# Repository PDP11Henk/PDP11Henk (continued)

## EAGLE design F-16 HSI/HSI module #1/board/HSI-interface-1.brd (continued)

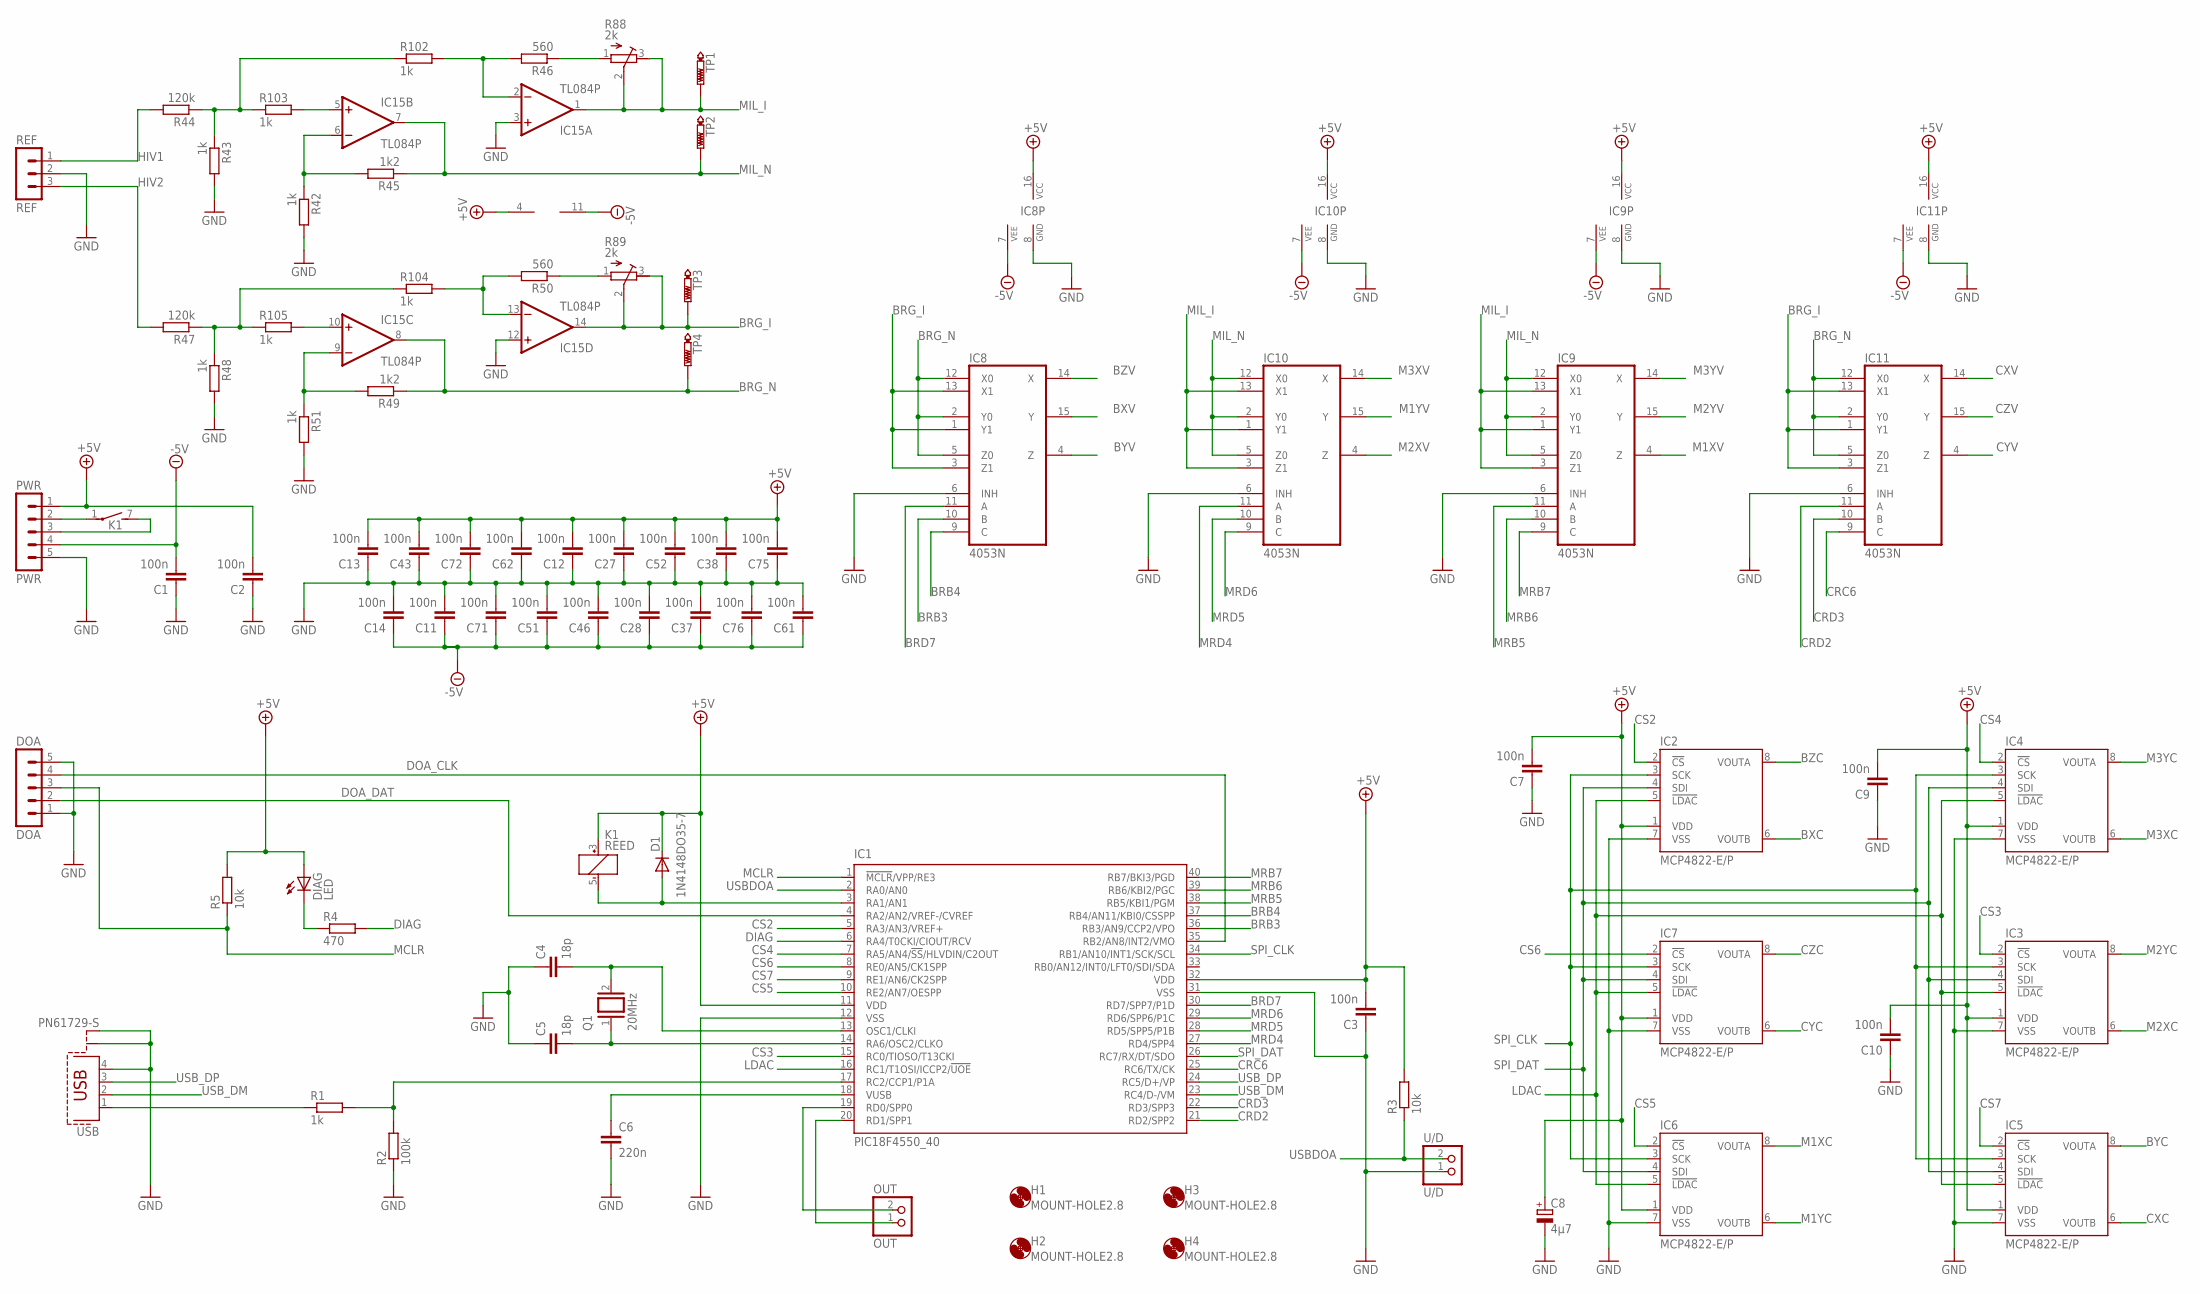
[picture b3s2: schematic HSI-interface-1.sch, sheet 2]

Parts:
C1, C2, C3, C7, C9, C10, C11, C12, C13, C14, C27, C28, C37, C38, C43, C46, C51, C52, C61, C62, C71, C72, C75, C76: 100n; C025-025X050
C4, C5: 18p; C025-025X050
C6: 220n; C5B3
C8: 4µ7; E2,5-5
D1: 1N4148DO35-7; DO35-7
DIAG: LED; LED3MM
DOA: DOA; MA05-1
H1, H2, H3, H4: MOUNT-HOLE2.8; 2,8
IC1: PIC18F4550_40; DIL40
IC2, IC3, IC4, IC5, IC6, IC7: MCP4822-E/P; DIL08
IC8, IC9, IC10, IC11: 4053N; DIL16
IC15: TL084P; DIL14
K1: REED
OUT: OUT; 1X02
PWR: PWR; MA05-1
Q1: 20MHz; QS
R1, R42, R43, R48, R51, R102, R103, R104, R105: 1k; 0204/7
R2: 100k; 0204/7
R3, R5: 10k; 0204/7
R4: 470; 0204/7
R44, R47: 120k; 0204/7
R45, R49: 1k2; 0204/7
R46, R50: 560; 0204/7
R88, R89: 2k; RTRIM64Z
REF: REF; MA03-1
TP1, TP2, TP3, TP4: PTR1PAD1-13; P1-13
U/D: U/D; 1X02
USB: PN61729-S

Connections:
+5V: C2.2, C3.2, C7.2, C8.+, C9.2, C10.2, C12.2, C13.2, C27.2, C38.2, C43.2, C52.2, C62.2, C72.2, C75.2, D1.C, DIAG.A, IC1.11 (VDD), IC1.32 (VDD), IC2.1 (VDD), IC3.1 (VDD), IC4.1 (VDD), IC5.1 (VDD), IC6.1 (VDD), IC7.1 (VDD), IC8.16 (VCC), IC9.16 (VCC), IC10.16 (VCC), IC11.16 (VCC), IC15.4 (V+), K1.3 (+), PWR.1, R3.2, R5.2; also elsewhere on the board
-5V: C1.2, C11.1, C14.1, C28.1, C37.1, C46.1, C51.1, C61.1, C71.1, C76.1, IC8.7 (VEE), IC9.7 (VEE), IC10.7 (VEE), IC11.7 (VEE), IC15.11 (V-), PWR.4; also elsewhere on the board
BRB3: IC1.36 (RB3/AN9/CCP2/VPO), IC8.10 (B)
BRB4: IC1.37 (RB4/AN11/KBI0/CSSPP), IC8.9 (C)
BRD7: IC1.30 (RD7/SPP7/P1D), IC8.11 (A)
BRG_I: IC8.1 (Y1), IC8.3 (Z1), IC8.13 (X1), IC11.1 (Y1), IC11.3 (Z1), IC11.13 (X1), IC15.14 (OUT), R89.2 (S), R89.3 (A), TP3.TP
BRG_N: IC8.2 (Y0), IC8.5 (Z0), IC8.12 (X0), IC11.2 (Y0), IC11.5 (Z0), IC11.12 (X0), IC15.8 (OUT), R49.1, TP4.TP
BXC: IC2.6 (VOUTB); also elsewhere on the board
BXV: IC8.15 (Y); also elsewhere on the board
BYC: IC5.8 (VOUTA); also elsewhere on the board
BYV: IC8.4 (Z); also elsewhere on the board
BZC: IC2.8 (VOUTA); also elsewhere on the board
BZV: IC8.14 (X); also elsewhere on the board
CRC6: IC1.25 (RC6/TX/CK), IC11.9 (C)
CRD2: IC1.21 (RD2/SPP2), IC11.11 (A)
CRD3: IC1.22 (RD3/SPP3), IC11.10 (B)
CS2: IC1.5 (RA3/AN3/VREF+), IC2.2 (!CS)
CS3: IC1.15 (RC0/TIOSO/T13CKI), IC3.2 (!CS)
CS4: IC1.7 (RA5/AN4/!SS!/HLVDIN/C2OUT), IC4.2 (!CS)
CS5: IC1.10 (RE2/AN7/OESPP), IC6.2 (!CS)
CS6: IC1.8 (RE0/AN5/CK1SPP), IC7.2 (!CS)
CS7: IC1.9 (RE1/AN6/CK2SPP), IC5.2 (!CS)
CXC: IC5.6 (VOUTB); also elsewhere on the board
CXV: IC11.14 (X); also elsewhere on the board
CYC: IC7.6 (VOUTB); also elsewhere on the board
CYV: IC11.4 (Z); also elsewhere on the board
CZC: IC7.8 (VOUTA); also elsewhere on the board
CZV: IC11.15 (Y); also elsewhere on the board
DIAG: IC1.6 (RA4/T0CKI/CIOUT/RCV), R4.2
DOA_CLK: DOA.4, IC1.35 (RB2/AN8/INT2/VMO)
DOA_DAT: DOA.2, IC1.4 (RA2/AN2/VREF-/CVREF)
GND: C1.1, C2.1, C3.1, C4.1, C5.1, C6.2, C7.1, C8.-, C9.1, C10.1, C11.2, C12.1, C13.1, C14.2, C27.1, C28.2, C37.2, C38.1, C43.1, C46.2, C51.2, C52.1, C61.2, C62.1, C71.2, C72.1, C75.1, C76.2, DOA.1, DOA.5, IC1.12 (VSS), IC1.31 (VSS), IC2.7 (VSS), IC3.7 (VSS), IC4.7 (VSS), IC5.7 (VSS), IC6.7 (VSS), IC7.7 (VSS), IC8.6 (INH), IC8.8 (GND), IC9.6 (INH), IC9.8 (GND), IC10.6 (INH), IC10.8 (GND), IC11.6 (INH), IC11.8 (GND), IC15.3 (+IN), IC15.12 (+IN), PWR.5, R2.1, R42.2, R43.2, R48.2, R51.2, REF.2, U/D.1, USB.4, USB.S1, USB.S2; also elsewhere on the board
HIV1: R44.2, REF.1
HIV2: R47.2, REF.3
LDAC: IC1.16 (RC1/T1OSI/ICCP2/!UOE), IC2.5 (!LDAC), IC3.5 (!LDAC), IC4.5 (!LDAC), IC5.5 (!LDAC), IC6.5 (!LDAC), IC7.5 (!LDAC)
M1XC: IC6.8 (VOUTA); also elsewhere on the board
M1XV: IC9.4 (Z); also elsewhere on the board
M1YC: IC6.6 (VOUTB); also elsewhere on the board
M1YV: IC10.15 (Y); also elsewhere on the board
M2XC: IC3.6 (VOUTB); also elsewhere on the board
M2XV: IC10.4 (Z); also elsewhere on the board
M2YC: IC3.8 (VOUTA); also elsewhere on the board
M2YV: IC9.15 (Y); also elsewhere on the board
M3XC: IC4.6 (VOUTB); also elsewhere on the board
M3XV: IC10.14 (X); also elsewhere on the board
M3YC: IC4.8 (VOUTA); also elsewhere on the board
M3YV: IC9.14 (X); also elsewhere on the board
MCLR: DOA.3, IC1.1 (!MCLR!/VPP/RE3), R5.1
MIL_I: IC9.1 (Y1), IC9.3 (Z1), IC9.13 (X1), IC10.1 (Y1), IC10.3 (Z1), IC10.13 (X1), IC15.1 (OUT), R88.2 (S), R88.3 (A), TP1.TP
MIL_N: IC9.2 (Y0), IC9.5 (Z0), IC9.12 (X0), IC10.2 (Y0), IC10.5 (Z0), IC10.12 (X0), IC15.7 (OUT), R45.1, TP2.TP
MRB5: IC1.38 (RB5/KBI1/PGM), IC9.11 (A)
MRB6: IC1.39 (RB6/KBI2/PGC), IC9.10 (B)
MRB7: IC1.40 (RB7/BKI3/PGD), IC9.9 (C)
MRD4: IC1.27 (RD4/SPP4), IC10.11 (A)
MRD5: IC1.28 (RD5/SPP5/P1B), IC10.10 (B)
MRD6: IC1.29 (RD6/SPP6/P1C), IC10.9 (C)
unnamed: IC1.20 (RD1/SPP1), OUT.1
unnamed: IC1.19 (RD0/SPP0), OUT.2
unnamed: IC15.6 (-IN), R42.1, R45.2
unnamed: IC15.2 (-IN), R46.2, R102.2
unnamed: IC15.5 (+IN), R103.2
unnamed: R50.1, R89.1 (E)
unnamed: R43.1, R44.1, R102.1, R103.1
unnamed: R46.1, R88.1 (E)
unnamed: D1.A, IC1.3 (RA1/AN1), K1.5 (-)
unnamed: R47.1, R48.1, R104.1, R105.1
unnamed: IC15.13 (-IN), R50.2, R104.2
unnamed: IC15.10 (+IN), R105.2
unnamed: IC15.9 (-IN), R49.2, R51.1
unnamed: R1.1, USB.1
unnamed: IC1.17 (RC2/CCP1/P1A), R1.2, R2.2
unnamed: C5.2, IC1.14 (RA6/OSC2/CLKO), Q1.1
unnamed: C4.2, IC1.13 (OSC1/CLKI), Q1.2
unnamed: K1.1, PWR.2
unnamed: K1.7 (S), PWR.3
unnamed: DIAG.K (C), R4.1
unnamed: C6.1, IC1.18 (VUSB)
SPI_CLK: IC1.34 (RB1/AN10/INT1/SCK/SCL), IC2.3 (SCK), IC3.3 (SCK), IC4.3 (SCK), IC5.3 (SCK), IC6.3 (SCK), IC7.3 (SCK)
SPI_DAT: IC1.26 (RC7/RX/DT/SDO), IC2.4 (SDI), IC3.4 (SDI), IC4.4 (SDI), IC5.4 (SDI), IC6.4 (SDI), IC7.4 (SDI)
USBDOA: IC1.2 (RA0/AN0), R3.1, U/D.2
USB_DM: IC1.23 (RC4/D-/VM), USB.2
USB_DP: IC1.24 (RC5/D+/VP), USB.3

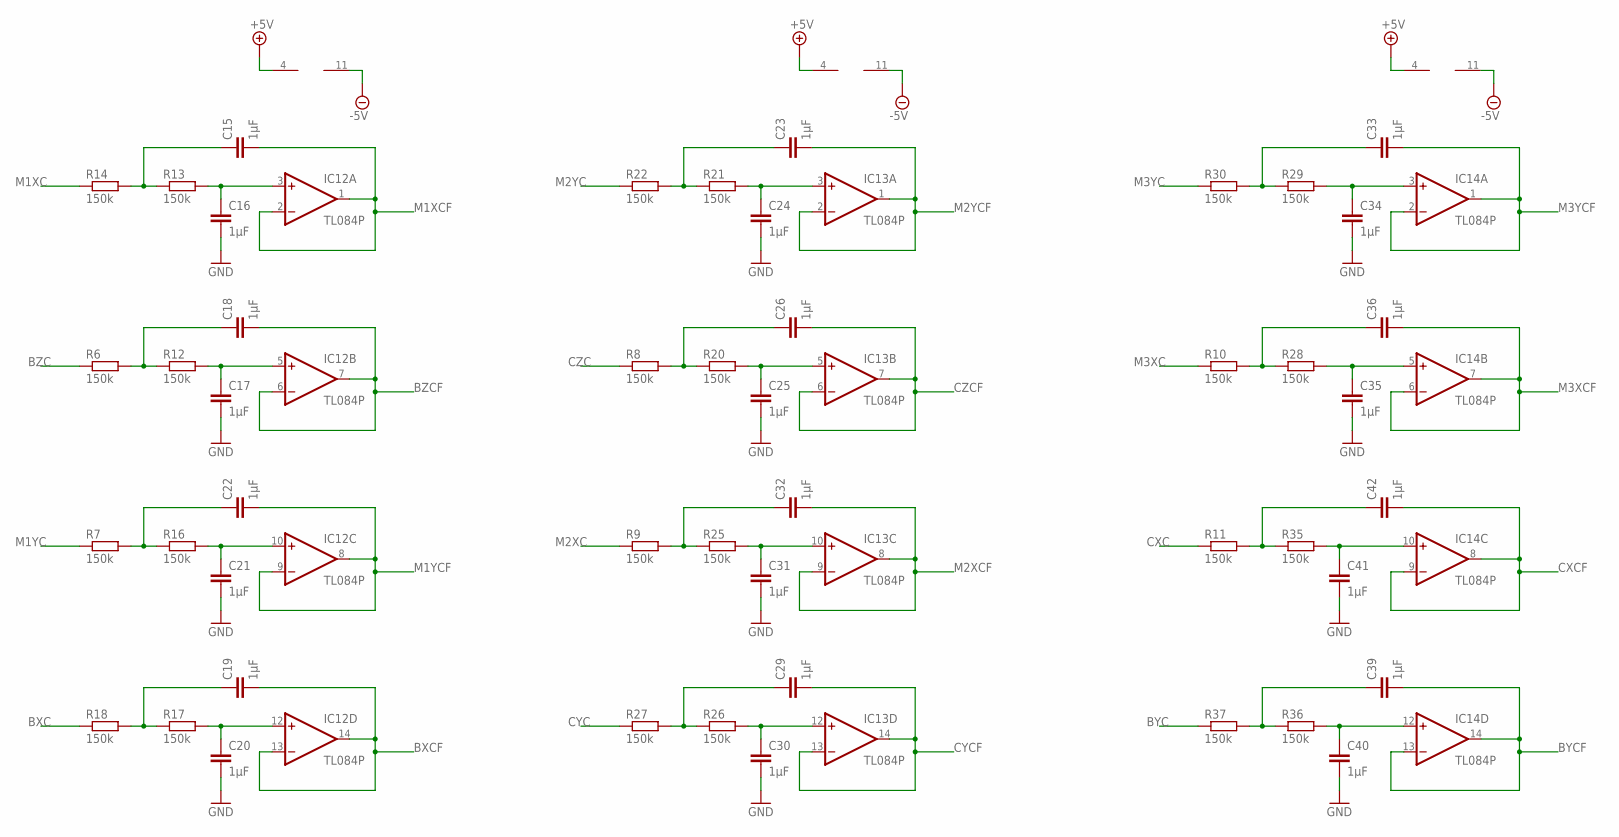
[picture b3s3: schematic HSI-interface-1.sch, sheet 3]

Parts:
C15, C16, C17, C18, C19, C20, C21, C22, C23, C24, C25, C26, C29, C30, C31, C32, C33, C34, C35, C36, C39, C40, C41, C42: 1µF; C025-025X050
IC12, IC13, IC14: TL084P; DIL14
R6, R7, R8, R9, R10, R11, R12, R13, R14, R16, R17, R18, R20, R21, R22, R25, R26, R27, R28, R29, R30, R35, R36, R37: 150k; 0207/7

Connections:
+5V: IC12.4 (V+), IC13.4 (V+), IC14.4 (V+); also elsewhere on the board
-5V: IC12.11 (V-), IC13.11 (V-), IC14.11 (V-); also elsewhere on the board
BXC: R18.1; also elsewhere on the board
BXCF: C19.2, IC12.13 (-IN), IC12.14 (OUT); also elsewhere on the board
BYC: R37.1; also elsewhere on the board
BYCF: C39.2, IC14.13 (-IN), IC14.14 (OUT); also elsewhere on the board
BZC: R6.1; also elsewhere on the board
BZCF: C18.2, IC12.6 (-IN), IC12.7 (OUT); also elsewhere on the board
CXC: R11.1; also elsewhere on the board
CXCF: C42.2, IC14.8 (OUT), IC14.9 (-IN); also elsewhere on the board
CYC: R27.1; also elsewhere on the board
CYCF: C29.2, IC13.13 (-IN), IC13.14 (OUT); also elsewhere on the board
CZC: R8.1; also elsewhere on the board
CZCF: C26.2, IC13.6 (-IN), IC13.7 (OUT); also elsewhere on the board
GND: C16.2, C17.2, C20.2, C21.2, C24.2, C25.2, C30.2, C31.2, C34.2, C35.2, C40.2, C41.2; also elsewhere on the board
M1XC: R14.1; also elsewhere on the board
M1XCF: C15.2, IC12.1 (OUT), IC12.2 (-IN); also elsewhere on the board
M1YC: R7.1; also elsewhere on the board
M1YCF: C22.2, IC12.8 (OUT), IC12.9 (-IN); also elsewhere on the board
M2XC: R9.1; also elsewhere on the board
M2XCF: C32.2, IC13.8 (OUT), IC13.9 (-IN); also elsewhere on the board
M2YC: R22.1; also elsewhere on the board
M2YCF: C23.2, IC13.1 (OUT), IC13.2 (-IN); also elsewhere on the board
M3XC: R10.1; also elsewhere on the board
M3XCF: C36.2, IC14.6 (-IN), IC14.7 (OUT); also elsewhere on the board
M3YC: R30.1; also elsewhere on the board
M3YCF: C33.2, IC14.1 (OUT), IC14.2 (-IN); also elsewhere on the board
unnamed: C15.1, R13.1, R14.2
unnamed: C16.1, IC12.3 (+IN), R13.2
unnamed: C18.1, R6.2, R12.1
unnamed: C17.1, IC12.5 (+IN), R12.2
unnamed: C21.1, IC12.10 (+IN), R16.2
unnamed: C22.1, R7.2, R16.1
unnamed: C19.1, R17.1, R18.2
unnamed: C20.1, IC12.12 (+IN), R17.2
unnamed: C33.1, R29.1, R30.2
unnamed: C34.1, IC14.3 (+IN), R29.2
unnamed: C36.1, R10.2, R28.1
unnamed: C35.1, IC14.5 (+IN), R28.2
unnamed: C42.1, R11.2, R35.1
unnamed: C41.1, IC14.10 (+IN), R35.2
unnamed: C39.1, R36.1, R37.2
unnamed: C40.1, IC14.12 (+IN), R36.2
unnamed: C24.1, IC13.3 (+IN), R21.2
unnamed: C23.1, R21.1, R22.2
unnamed: C26.1, R8.2, R20.1
unnamed: C25.1, IC13.5 (+IN), R20.2
unnamed: C32.1, R9.2, R25.1
unnamed: C31.1, IC13.10 (+IN), R25.2
unnamed: C30.1, IC13.12 (+IN), R26.2
unnamed: C29.1, R26.1, R27.2

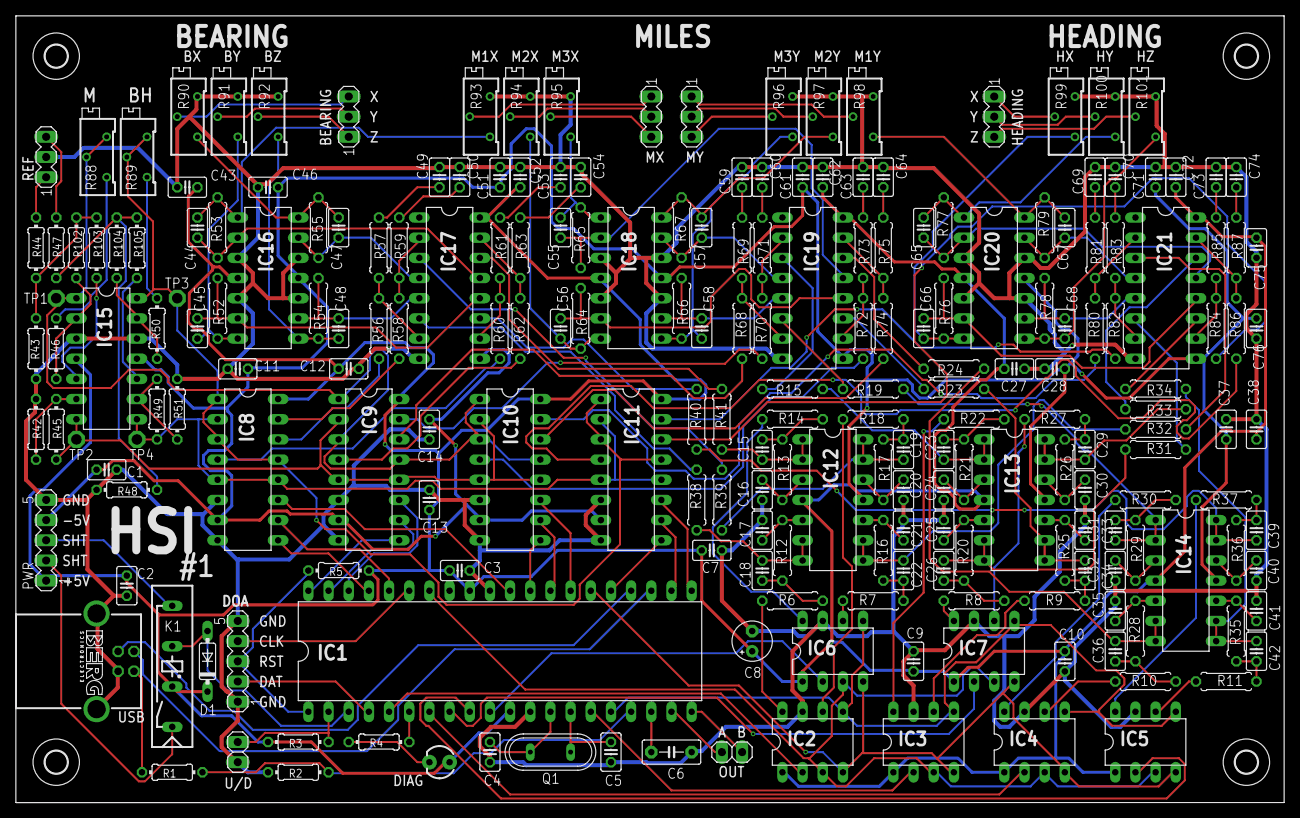
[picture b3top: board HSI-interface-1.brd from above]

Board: 2 copper layers, 159.7 x 99.1 mm, 224 parts (0 on the bottom side), 190 nets.

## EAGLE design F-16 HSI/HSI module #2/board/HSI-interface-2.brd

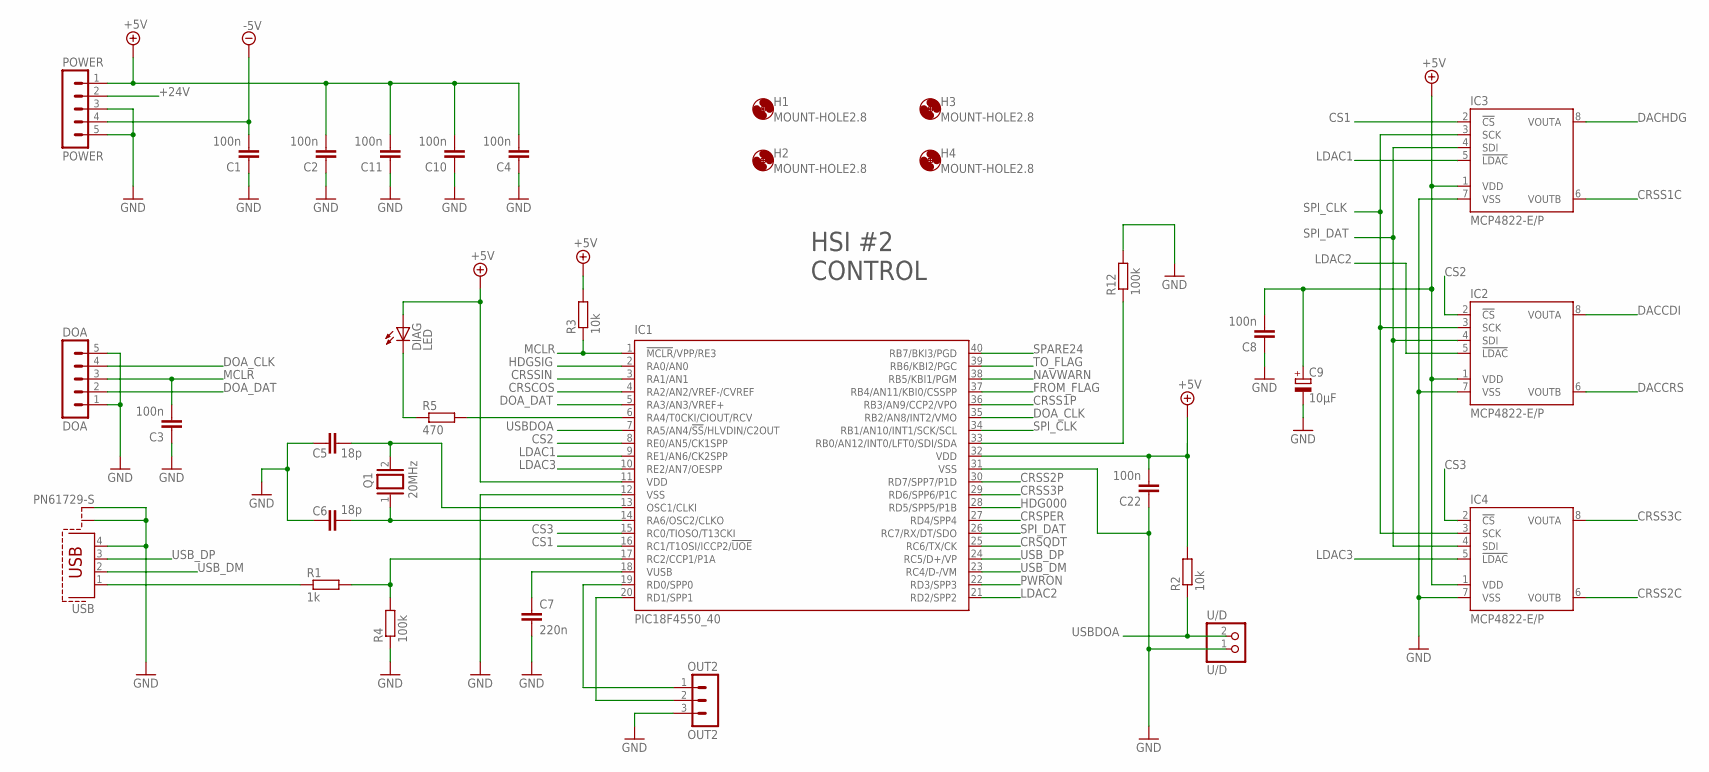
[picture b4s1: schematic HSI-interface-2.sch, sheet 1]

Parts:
C1, C2, C3, C4, C8, C10, C11, C22: 100n; C025-025X050
C5, C6: 18p; C025-025X050
C7: 220n; C5B3
C9: 10µF; E2,5-5
DIAG: LED; LED3MM
DOA: DOA; MA05-1
H1, H2, H3, H4: MOUNT-HOLE2.8; 2,8
IC1: PIC18F4550_40; DIL40
IC2, IC3, IC4: MCP4822-E/P; DIL08
OUT2: OUT2; MA03-1
POWER: POWER; MA05-1
Q1: 20MHz; QS
R1: 1k; 0204/7
R2, R3: 10k; 0204/7
R4, R12: 100k; 0204/7
R5: 470; 0204/7
U/D: U/D; 1X02
USB: PN61729-S

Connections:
+5V: C2.2, C4.2, C8.2, C9.+, C10.2, C11.2, C22.2, DIAG.A, IC1.11 (VDD), IC1.32 (VDD), IC2.1 (VDD), IC3.1 (VDD), IC4.1 (VDD), POWER.1, R2.2, R3.2; also elsewhere on the board
+24V: POWER.2; also elsewhere on the board
-5V: C1.2, POWER.4; also elsewhere on the board
CRSCOS: IC1.4 (RA2/AN2/VREF-/CVREF); also elsewhere on the board
CRSPER: IC1.27 (RD4/SPP4); also elsewhere on the board
CRSQDT: IC1.25 (RC6/TX/CK); also elsewhere on the board
CRSS1C: IC3.6 (VOUTB); also elsewhere on the board
CRSS1P: IC1.36 (RB3/AN9/CCP2/VPO); also elsewhere on the board
CRSS2C: IC4.6 (VOUTB); also elsewhere on the board
CRSS2P: IC1.30 (RD7/SPP7/P1D); also elsewhere on the board
CRSS3C: IC4.8 (VOUTA); also elsewhere on the board
CRSS3P: IC1.29 (RD6/SPP6/P1C); also elsewhere on the board
CRSSIN: IC1.3 (RA1/AN1); also elsewhere on the board
CS1: IC1.16 (RC1/T1OSI/ICCP2/!UOE), IC3.2 (!CS)
CS2: IC1.8 (RE0/AN5/CK1SPP), IC2.2 (!CS)
CS3: IC1.15 (RC0/TIOSO/T13CKI), IC4.2 (!CS)
DACCDI: IC2.8 (VOUTA); also elsewhere on the board
DACCRS: IC2.6 (VOUTB); also elsewhere on the board
DACHDG: IC3.8 (VOUTA); also elsewhere on the board
DOA_CLK: DOA.4, IC1.35 (RB2/AN8/INT2/VMO)
DOA_DAT: DOA.2, IC1.5 (RA3/AN3/VREF+)
FROM_FLAG: IC1.37 (RB4/AN11/KBI0/CSSPP); also elsewhere on the board
GND: C1.1, C2.1, C3.1, C4.1, C5.1, C6.1, C7.2, C8.1, C9.-, C10.1, C11.1, C22.1, DOA.1, DOA.5, IC1.12 (VSS), IC1.31 (VSS), IC2.7 (VSS), IC3.7 (VSS), IC4.7 (VSS), OUT2.3, POWER.3, POWER.5, R4.1, R12.2, U/D.1, USB.4, USB.S1, USB.S2; also elsewhere on the board
HDG000: IC1.28 (RD5/SPP5/P1B); also elsewhere on the board
HDGSIG: IC1.2 (RA0/AN0); also elsewhere on the board
LDAC1: IC1.9 (RE1/AN6/CK2SPP), IC3.5 (!LDAC)
LDAC2: IC1.21 (RD2/SPP2), IC2.5 (!LDAC)
LDAC3: IC1.10 (RE2/AN7/OESPP), IC4.5 (!LDAC)
MCLR: C3.2, DOA.3, IC1.1 (!MCLR!/VPP/RE3), R3.1
unnamed: IC1.20 (RD1/SPP1), OUT2.2
unnamed: IC1.19 (RD0/SPP0), OUT2.1
unnamed: DIAG.K (C), R5.1
unnamed: IC1.6 (RA4/T0CKI/CIOUT/RCV), R5.2
unnamed: R1.1, USB.1
unnamed: IC1.17 (RC2/CCP1/P1A), R1.2, R4.2
unnamed: C6.2, IC1.14 (RA6/OSC2/CLKO), Q1.1
unnamed: C5.2, IC1.13 (OSC1/CLKI), Q1.2
unnamed: C7.1, IC1.18 (VUSB)
unnamed: IC1.33 (RB0/AN12/INT0/LFT0/SDI/SDA), R12.1
NAVWARN: IC1.38 (RB5/KBI1/PGM); also elsewhere on the board
PWRON: IC1.22 (RD3/SPP3); also elsewhere on the board
SPARE24: IC1.40 (RB7/BKI3/PGD); also elsewhere on the board
SPI_CLK: IC1.34 (RB1/AN10/INT1/SCK/SCL), IC2.3 (SCK), IC3.3 (SCK), IC4.3 (SCK)
SPI_DAT: IC1.26 (RC7/RX/DT/SDO), IC2.4 (SDI), IC3.4 (SDI), IC4.4 (SDI)
TO_FLAG: IC1.39 (RB6/KBI2/PGC); also elsewhere on the board
USBDOA: IC1.7 (RA5/AN4/!SS!/HLVDIN/C2OUT), R2.1, U/D.2
USB_DM: IC1.23 (RC4/D-/VM), USB.2
USB_DP: IC1.24 (RC5/D+/VP), USB.3

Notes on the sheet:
HSI #2 CONTROL

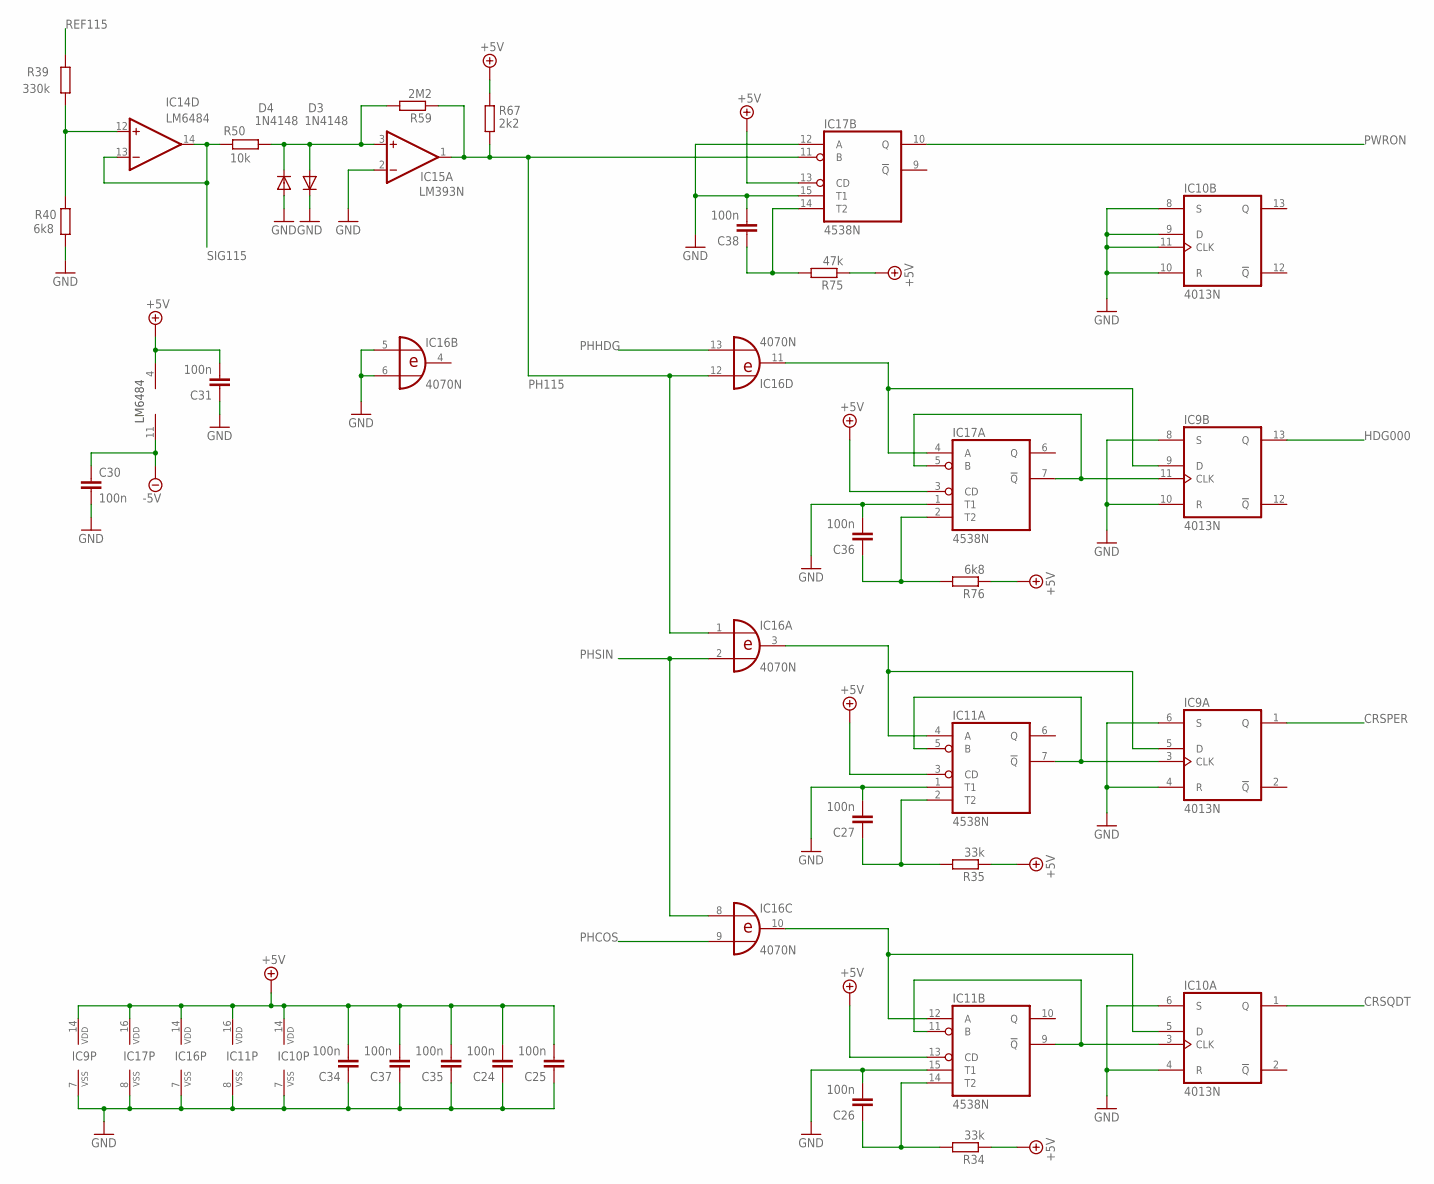
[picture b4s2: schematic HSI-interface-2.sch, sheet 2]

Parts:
C24, C25, C26, C27, C30, C31, C34, C35, C36, C37, C38: 100n; C025-025X050
D3, D4: 1N4148; DO35-7
IC9, IC10: 4013N; DIL14
IC11, IC17: 4538N; DIL16
IC14: LM6484; DIL14
IC15: LM393N; DIL08
IC16: 4070N; DIL14
R34, R35: 33k; 0204/7
R39: 330k; 0204/7
R40, R76: 6k8; 0204/7
R50: 10k; 0204/7
R59: 2M2; 0204/7
R67: 2k2; 0204/7
R75: 47k; 0204/7

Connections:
+5V: C24.2, C25.2, C31.2, C34.2, C35.2, C37.2, IC9.14 (VDD), IC10.14 (VDD), IC11.3 (CD), IC11.13 (CD), IC11.16 (VDD), IC14.4 (V+), IC16.14 (VDD), IC17.3 (CD), IC17.13 (CD), IC17.16 (VDD), R34.1, R35.1, R67.2, R75.1, R76.1; also elsewhere on the board
-5V: C30.1, IC14.11 (V-); also elsewhere on the board
CRSPER: IC9.1 (Q); also elsewhere on the board
CRSQDT: IC10.1 (Q); also elsewhere on the board
GND: C24.1, C25.1, C26.2, C27.2, C30.2, C31.1, C34.1, C35.1, C36.2, C37.1, C38.2, D3.C, D4.A, IC9.4 (R), IC9.6 (S), IC9.7 (VSS), IC9.8 (S), IC9.10 (R), IC10.4 (R), IC10.6 (S), IC10.7 (VSS), IC10.8 (S), IC10.9 (D), IC10.10 (R), IC10.11 (CLK), IC11.1 (T1), IC11.8 (VSS), IC11.15 (T1), IC15.2 (-IN), IC16.5 (I0), IC16.6 (I1), IC16.7 (VSS), IC17.1 (T1), IC17.8 (VSS), IC17.12 (A), IC17.15 (T1), R40.1; also elsewhere on the board
HDG000: IC9.13 (Q); also elsewhere on the board
unnamed: IC9.11 (CLK), IC17.5 (B), IC17.7 (!Q)
unnamed: IC14.12 (+IN), R39.1, R40.2
unnamed: IC9.9 (D), IC16.11 (O), IC17.4 (A)
unnamed: IC10.5 (D), IC11.12 (A), IC16.10 (O)
unnamed: IC9.5 (D), IC11.4 (A), IC16.3 (O)
unnamed: IC9.3 (CLK), IC11.5 (B), IC11.7 (!Q)
unnamed: D3.A, D4.C, IC15.3 (+IN), R50.1, R59.2
unnamed: C38.1, IC17.14 (T2), R75.2
unnamed: C36.1, IC17.2 (T2), R76.2
unnamed: IC10.3 (CLK), IC11.9 (!Q), IC11.11 (B)
unnamed: C27.1, IC11.2 (T2), R35.2
unnamed: C26.1, IC11.14 (T2), R34.2
PH115: IC15.1 (OUT), IC16.1 (I0), IC16.12 (I0), IC17.11 (B), R59.1, R67.1
PHCOS: IC16.9 (I1); also elsewhere on the board
PHHDG: IC16.13 (I1); also elsewhere on the board
PHSIN: IC16.2 (I1), IC16.8 (I0); also elsewhere on the board
PWRON: IC17.10 (Q); also elsewhere on the board
REF115: R39.2; also elsewhere on the board
SIG115: IC14.13 (-IN), IC14.14 (OUT), R50.2; also elsewhere on the board

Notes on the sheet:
LM6484

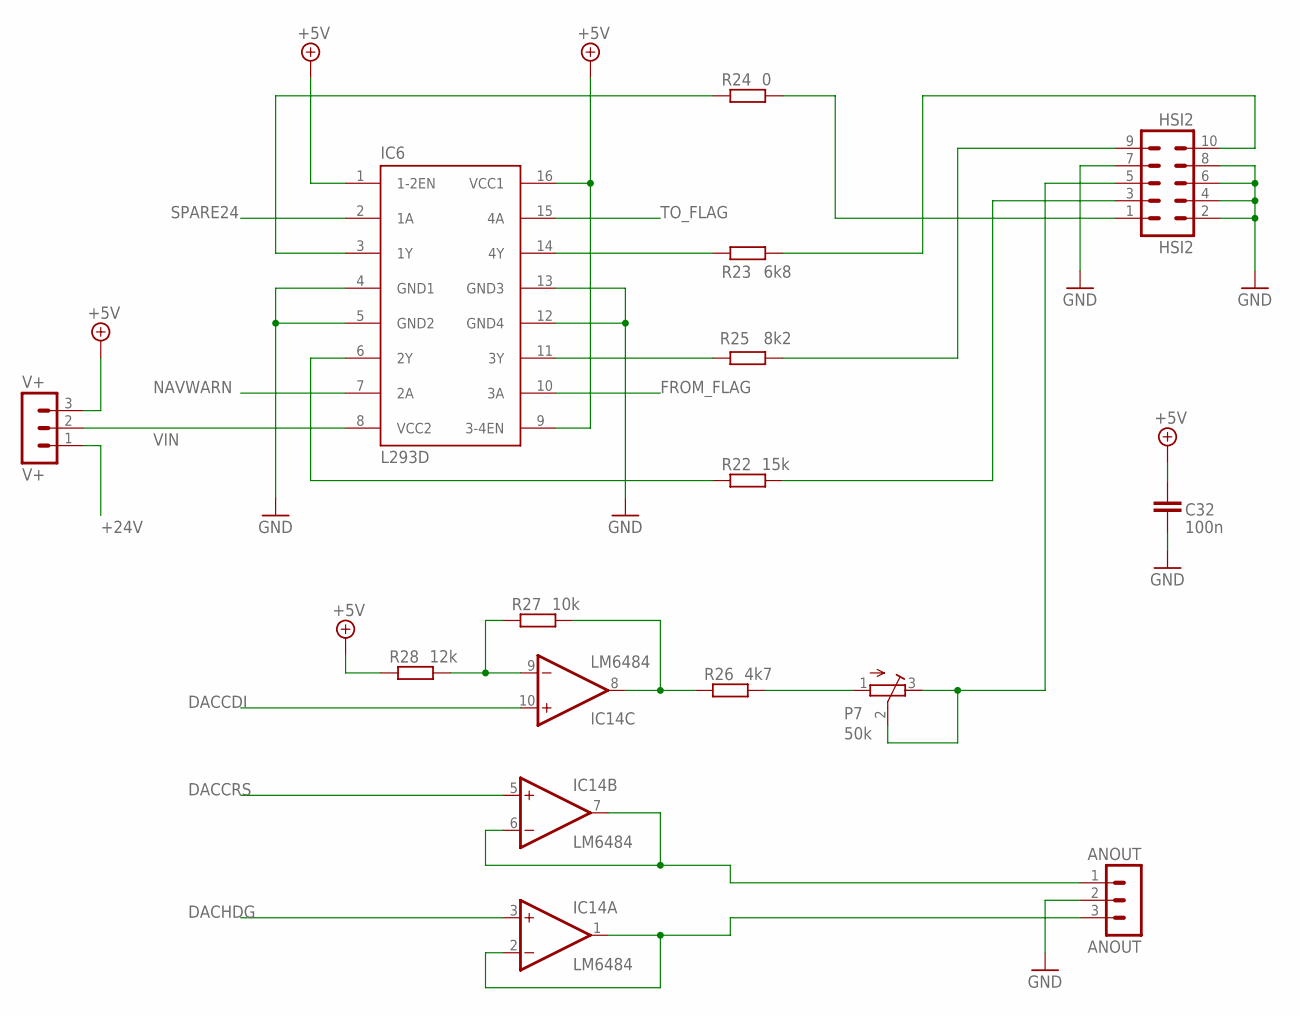
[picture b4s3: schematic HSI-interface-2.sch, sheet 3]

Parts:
ANOUT: ANOUT; MA03-1
C32: 100n; C025-025X050
HSI2: HSI2; MA05-2
IC6: L293D; DIL16
IC14: LM6484; DIL14
P7: 50k; RTRIM64Z
R22: 15k; 0204/7
R23: 6k8; 0204/7
R24: 0; 0204/7
R25: 8k2; 0204/7
R26: 4k7; 0204/7
R27: 10k; 0204/7
R28: 12k; 0204/7
V+: V+; MA03-1

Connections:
+5V: C32.2, IC6.1 (1-2EN), IC6.9 (3-4EN), IC6.16 (VCC1), R28.1, V+.3; also elsewhere on the board
+24V: V+.1; also elsewhere on the board
DACCDI: IC14.10 (+IN); also elsewhere on the board
DACCRS: IC14.5 (+IN); also elsewhere on the board
DACHDG: IC14.3 (+IN); also elsewhere on the board
FROM_FLAG: IC6.10 (3A); also elsewhere on the board
GND: ANOUT.2, C32.1, HSI2.2, HSI2.4, HSI2.6, HSI2.7, HSI2.8, IC6.4 (GND1), IC6.5 (GND2), IC6.12 (GND4), IC6.13 (GND3); also elsewhere on the board
unnamed: HSI2.3, R22.2
unnamed: HSI2.1, R24.2
unnamed: IC14.8 (OUT), R26.1, R27.2
unnamed: HSI2.5, P7.2 (S), P7.3 (A)
unnamed: ANOUT.1, IC14.6 (-IN), IC14.7 (OUT)
unnamed: HSI2.10, R23.2
unnamed: IC6.14 (4Y), R23.1
unnamed: HSI2.9, R25.2
unnamed: IC6.6 (2Y), R22.1
unnamed: IC14.9 (-IN), R27.1, R28.2
unnamed: IC6.3 (1Y), R24.1
unnamed: P7.1 (E), R26.2
unnamed: ANOUT.3, IC14.1 (OUT), IC14.2 (-IN)
unnamed: IC6.11 (3Y), R25.1
NAVWARN: IC6.7 (2A); also elsewhere on the board
SPARE24: IC6.2 (1A); also elsewhere on the board
TO_FLAG: IC6.15 (4A); also elsewhere on the board
VIN: IC6.8 (VCC2), V+.2

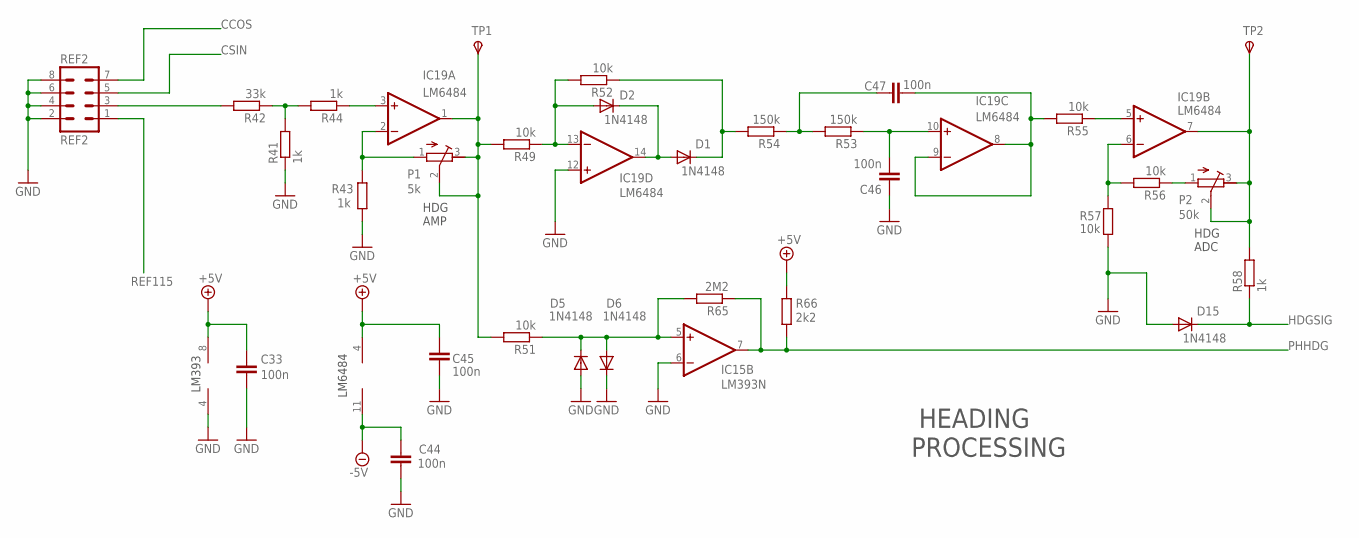
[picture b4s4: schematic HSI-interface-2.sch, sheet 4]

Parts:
C33, C44, C45, C46, C47: 100n; C025-025X050
D1, D2, D5, D6, D15: 1N4148; DO35-7
IC15: LM393N; DIL08
IC19: LM6484; DIL14
P1: 5k; RTRIM64Z
P2: 50k; RTRIM64Z
R41, R43, R44, R58: 1k; 0204/7
R42: 33k; 0204/7
R49, R51, R52, R55, R56, R57: 10k; 0204/7
R53, R54: 150k; 0204/7
R65: 2M2; 0204/7
R66: 2k2; 0204/7
REF2: REF2; MA04-2
TP1, TP2: TPSPAD1-13; P1-13

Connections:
+5V: C33.2, C45.2, IC15.8 (V+), IC19.4 (V+), R66.2; also elsewhere on the board
-5V: C44.2, IC19.11 (V-); also elsewhere on the board
CCOS: REF2.7; also elsewhere on the board
CSIN: REF2.5; also elsewhere on the board
GND: C33.1, C44.1, C45.1, C46.1, D5.A, D6.C, D15.A, IC15.4 (V-), IC15.6 (-IN), IC19.12 (+IN), R41.1, R43.1, R57.2, REF2.2, REF2.4, REF2.6, REF2.8; also elsewhere on the board
HDGSIG: D15.C, R58.1; also elsewhere on the board
unnamed: IC19.3 (+IN), R44.1
unnamed: R42.2, REF2.3
unnamed: R41.2, R42.1, R44.2
unnamed: IC19.2 (-IN), P1.1 (E), R43.2
unnamed: IC19.1 (OUT), P1.2 (S), P1.3 (A), R49.2, R51.2, TP1.TP
unnamed: D1.A, D2.C, IC19.14 (OUT)
unnamed: D2.A, IC19.13 (-IN), R49.1, R52.2
unnamed: D1.C, R52.1, R54.2
unnamed: C47.1, R53.2, R54.1
unnamed: C46.2, IC19.10 (+IN), R53.1
unnamed: C47.2, IC19.8 (OUT), IC19.9 (-IN), R55.2
unnamed: IC19.5 (+IN), R55.1
unnamed: IC19.6 (-IN), R56.2, R57.1
unnamed: P2.1 (E), R56.1
unnamed: D5.C, D6.A, IC15.5 (+IN), R51.1, R65.2
unnamed: IC19.7 (OUT), P2.2 (S), P2.3 (A), R58.2, TP2.TP
PHHDG: IC15.7 (OUT), R65.1, R66.1; also elsewhere on the board
REF115: REF2.1; also elsewhere on the board

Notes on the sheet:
LM6484
LM393
HEADING PROCESSING
HDG AMP
HDG ADC

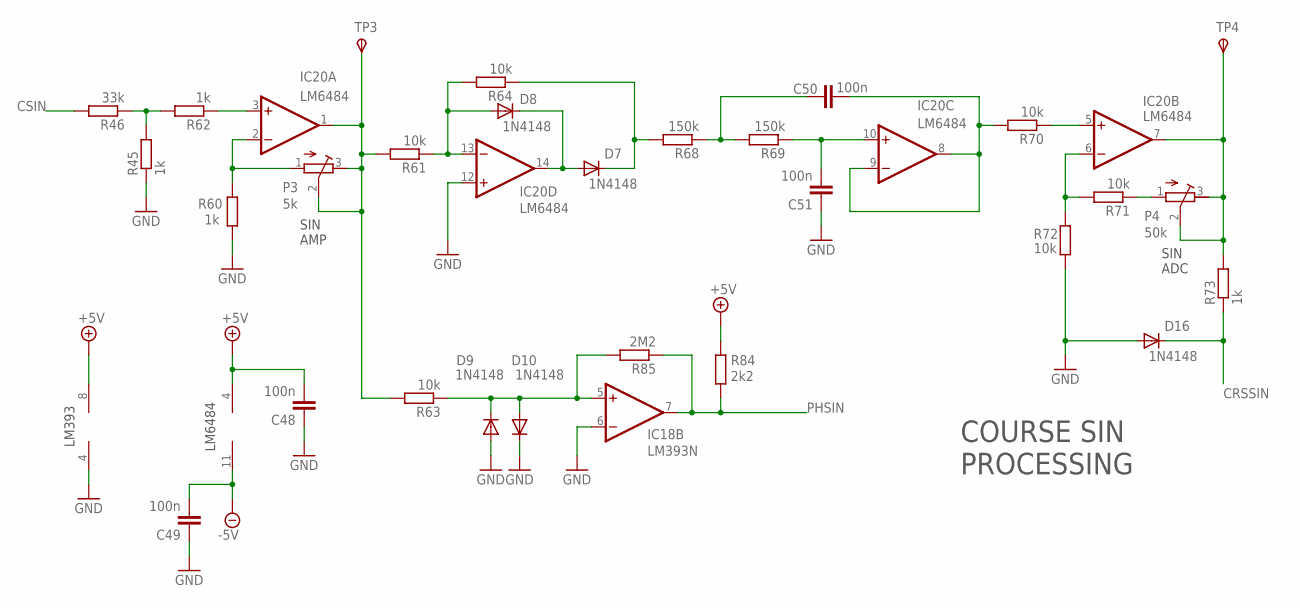
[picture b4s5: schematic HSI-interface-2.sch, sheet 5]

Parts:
C48, C49, C50, C51: 100n; C025-025X050
D7, D8, D9, D10, D16: 1N4148; DO35-7
IC18: LM393N; DIL08
IC20: LM6484; DIL14
P3: 5k; RTRIM64Z
P4: 50k; RTRIM64Z
R45, R60, R62, R73: 1k; 0204/7
R46: 33k; 0204/7
R61, R63, R64, R70, R71, R72: 10k; 0204/7
R68, R69: 150k; 0204/7
R84: 2k2; 0204/7
R85: 2M2; 0204/7
TP3, TP4: TPSPAD1-13; P1-13

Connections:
+5V: C48.2, IC18.8 (V+), IC20.4 (V+), R84.2; also elsewhere on the board
-5V: C49.2, IC20.11 (V-); also elsewhere on the board
CRSSIN: D16.C, R73.1; also elsewhere on the board
CSIN: R46.2; also elsewhere on the board
GND: C48.1, C49.1, C51.1, D9.A, D10.C, D16.A, IC18.4 (V-), IC18.6 (-IN), IC20.12 (+IN), R45.1, R60.1, R72.2; also elsewhere on the board
unnamed: R45.2, R46.1, R62.2
unnamed: IC20.2 (-IN), P3.1 (E), R60.2
unnamed: IC20.1 (OUT), P3.2 (S), P3.3 (A), R61.2, R63.2, TP3.TP
unnamed: D7.A, D8.C, IC20.14 (OUT)
unnamed: D8.A, IC20.13 (-IN), R61.1, R64.2
unnamed: D7.C, R64.1, R68.2
unnamed: C50.1, R68.1, R69.2
unnamed: C51.2, IC20.10 (+IN), R69.1
unnamed: C50.2, IC20.8 (OUT), IC20.9 (-IN), R70.2
unnamed: IC20.5 (+IN), R70.1
unnamed: IC20.6 (-IN), R71.2, R72.1
unnamed: P4.1 (E), R71.1
unnamed: IC20.3 (+IN), R62.1
unnamed: D9.C, D10.A, IC18.5 (+IN), R63.1, R85.2
unnamed: IC20.7 (OUT), P4.2 (S), P4.3 (A), R73.2, TP4.TP
PHSIN: IC18.7 (OUT), R84.1, R85.1; also elsewhere on the board

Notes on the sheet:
LM6484
SIN AMP
SIN ADC
COURSE SIN PROCESSING
LM393
